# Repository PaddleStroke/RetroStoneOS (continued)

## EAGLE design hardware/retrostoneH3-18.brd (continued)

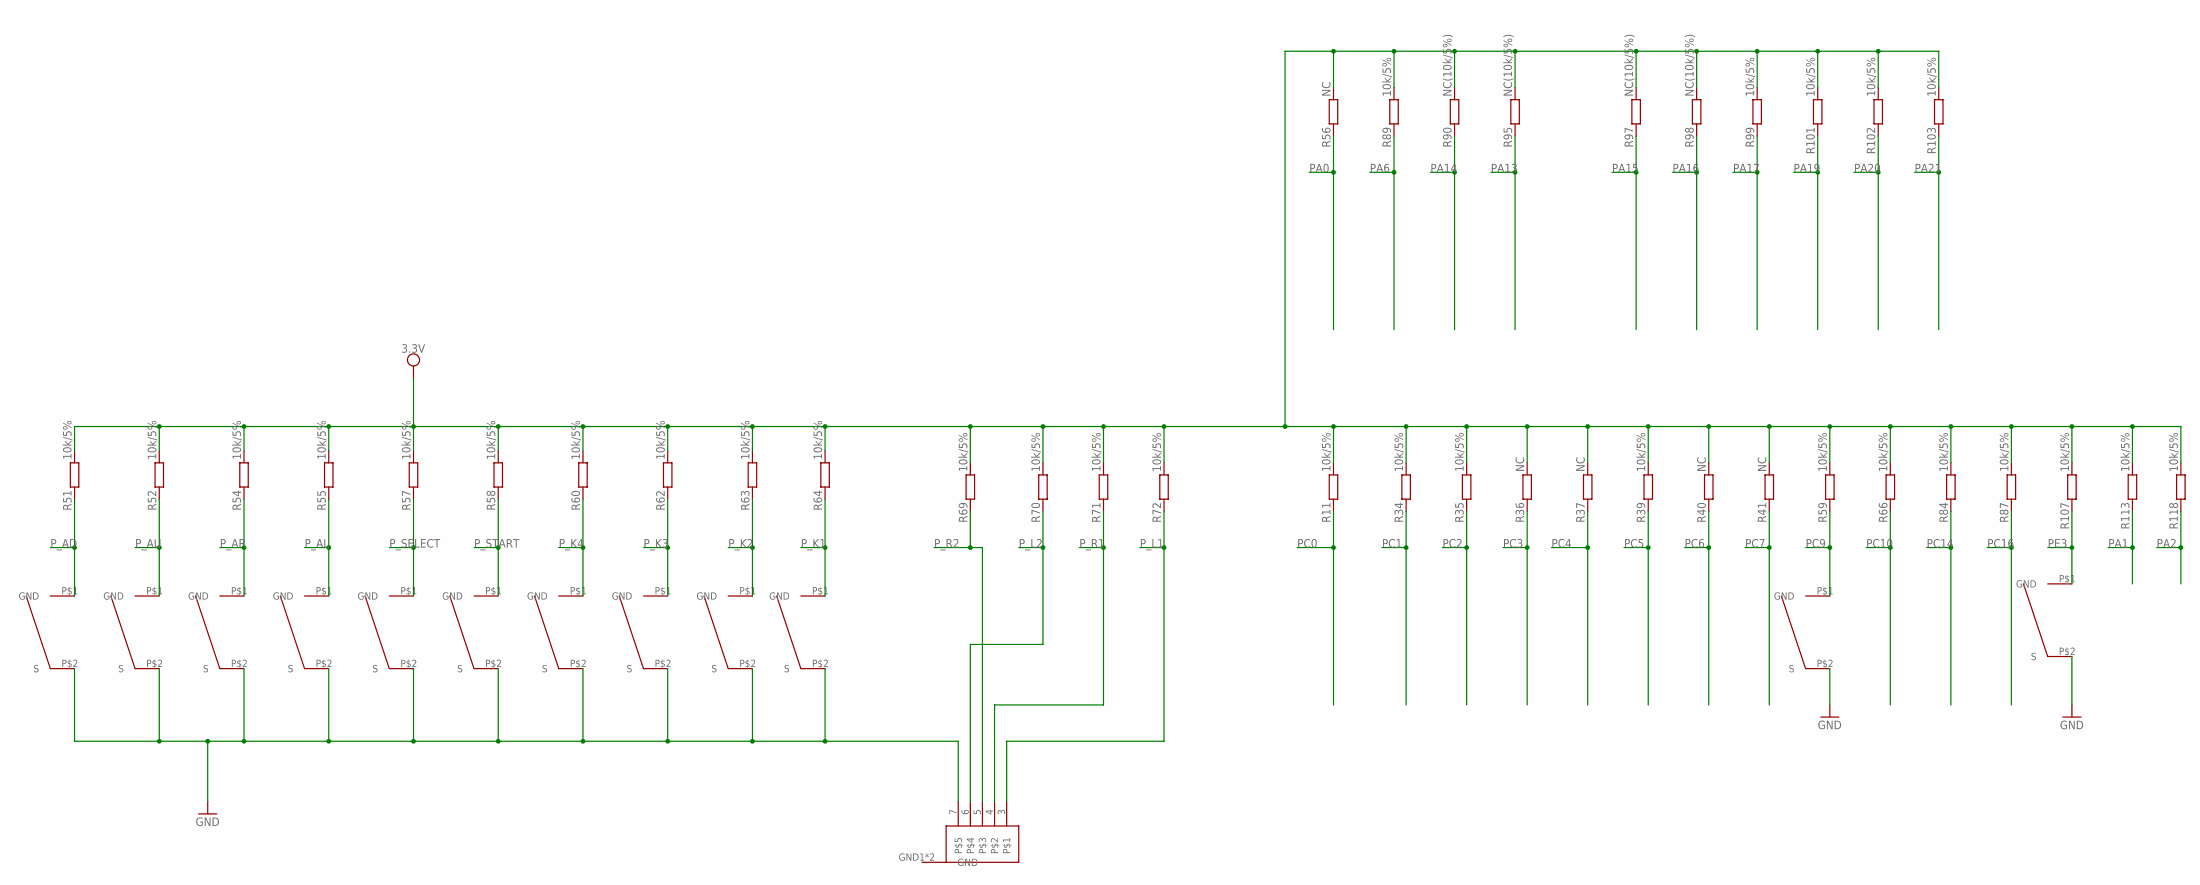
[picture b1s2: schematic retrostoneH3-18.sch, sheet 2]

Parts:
AD: PAD_DIRECTION; PADS_DIRECTION
AL: PAD_DIRECTION; PADS_DIRECTION
AR: PAD_DIRECTION; PADS_DIRECTION
AU: PAD_DIRECTION; PADS_DIRECTION
K1, K2, K3, K4: PAD_BUTTON
R11, R34, R35, R39, R51, R52, R54, R55, R57, R58, R59, R60, R62, R63, R64, R66, R69, R70, R71, R72, R84, R87, R89, R99, R101, R102, R103, R107, R113, R118: 10k/5%; R0402_TI
R36, R37, R40, R41, R56: NC; R0402_TI
R90, R95, R97, R98: NC(10k/5%); R0402_TI
SELECT, SELECT3, SELECT4: PAD_BUTTON
START: PAD_BUTTON
U$4: JST_PH_VERT_5P

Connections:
GND: AD.P$2 (S), AL.P$2 (S), AR.P$2 (S), AU.P$2 (S), K1.P$2 (S), K2.P$2 (S), K3.P$2 (S), K4.P$2 (S), SELECT.P$2 (S), SELECT3.P$2 (S), SELECT4.P$2 (S), START.P$2 (S), U$4.7; also elsewhere on the board
PA0: R56.2; also elsewhere on the board
PA1: R113.2; also elsewhere on the board
PA2: R118.2; also elsewhere on the board
PA6: R89.2; also elsewhere on the board
PA13: R95.2; also elsewhere on the board
PA14: R90.2; also elsewhere on the board
PA15: R97.2; also elsewhere on the board
PA16: R98.2; also elsewhere on the board
PA17: R99.2; also elsewhere on the board
PA19: R101.2; also elsewhere on the board
PA20: R102.2; also elsewhere on the board
PA21: R103.2; also elsewhere on the board
PC0: R11.2; also elsewhere on the board
PC1: R34.2; also elsewhere on the board
PC2: R35.2; also elsewhere on the board
PC3: R36.2; also elsewhere on the board
PC4: R37.2; also elsewhere on the board
PC5: R39.2; also elsewhere on the board
PC6: R40.2; also elsewhere on the board
PC7: R41.2; also elsewhere on the board
PC9: R59.2, SELECT4.P$1 (GND); also elsewhere on the board
PC10: R66.2; also elsewhere on the board
PC14: R84.2; also elsewhere on the board
PC16: R87.2; also elsewhere on the board
PE3: R107.2, SELECT3.P$1 (GND); also elsewhere on the board
P_AD: AD.P$1 (GND), R51.2; also elsewhere on the board
P_AL: AL.P$1 (GND), R55.2; also elsewhere on the board
P_AR: AR.P$1 (GND), R54.2; also elsewhere on the board
P_AU: AU.P$1 (GND), R52.2; also elsewhere on the board
P_K1: K1.P$1 (GND), R64.2; also elsewhere on the board
P_K2: K2.P$1 (GND), R63.2; also elsewhere on the board
P_K3: K3.P$1 (GND), R62.2; also elsewhere on the board
P_K4: K4.P$1 (GND), R60.2; also elsewhere on the board
P_L1: R72.2, U$4.3; also elsewhere on the board
P_L2: R70.2, U$4.6; also elsewhere on the board
P_R1: R71.2, U$4.4; also elsewhere on the board
P_R2: R69.2, U$4.5; also elsewhere on the board
P_SELECT: R57.2, SELECT.P$1 (GND); also elsewhere on the board
P_START: R58.2, START.P$1 (GND); also elsewhere on the board
VCC: R11.1, R34.1, R35.1, R36.1, R37.1, R39.1, R40.1, R41.1, R51.1, R52.1, R54.1, R55.1, R56.1, R57.1, R58.1, R59.1, R60.1, R62.1, R63.1, R64.1, R66.1, R69.1, R70.1, R71.1, R72.1, R84.1, R87.1, R89.1, R90.1, R95.1, R97.1, R98.1, R99.1, R101.1, R102.1, R103.1, R107.1, R113.1, R118.1; also elsewhere on the board

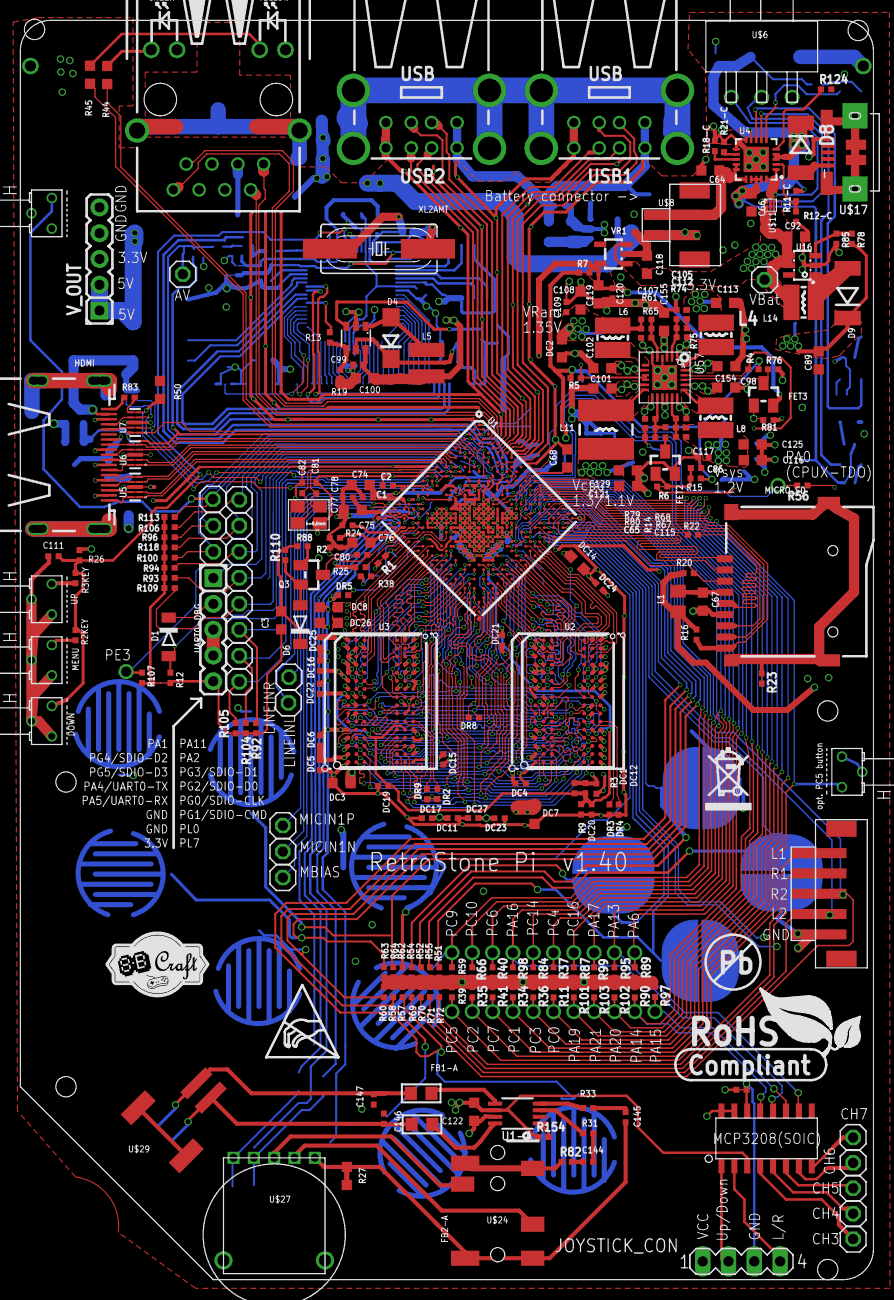
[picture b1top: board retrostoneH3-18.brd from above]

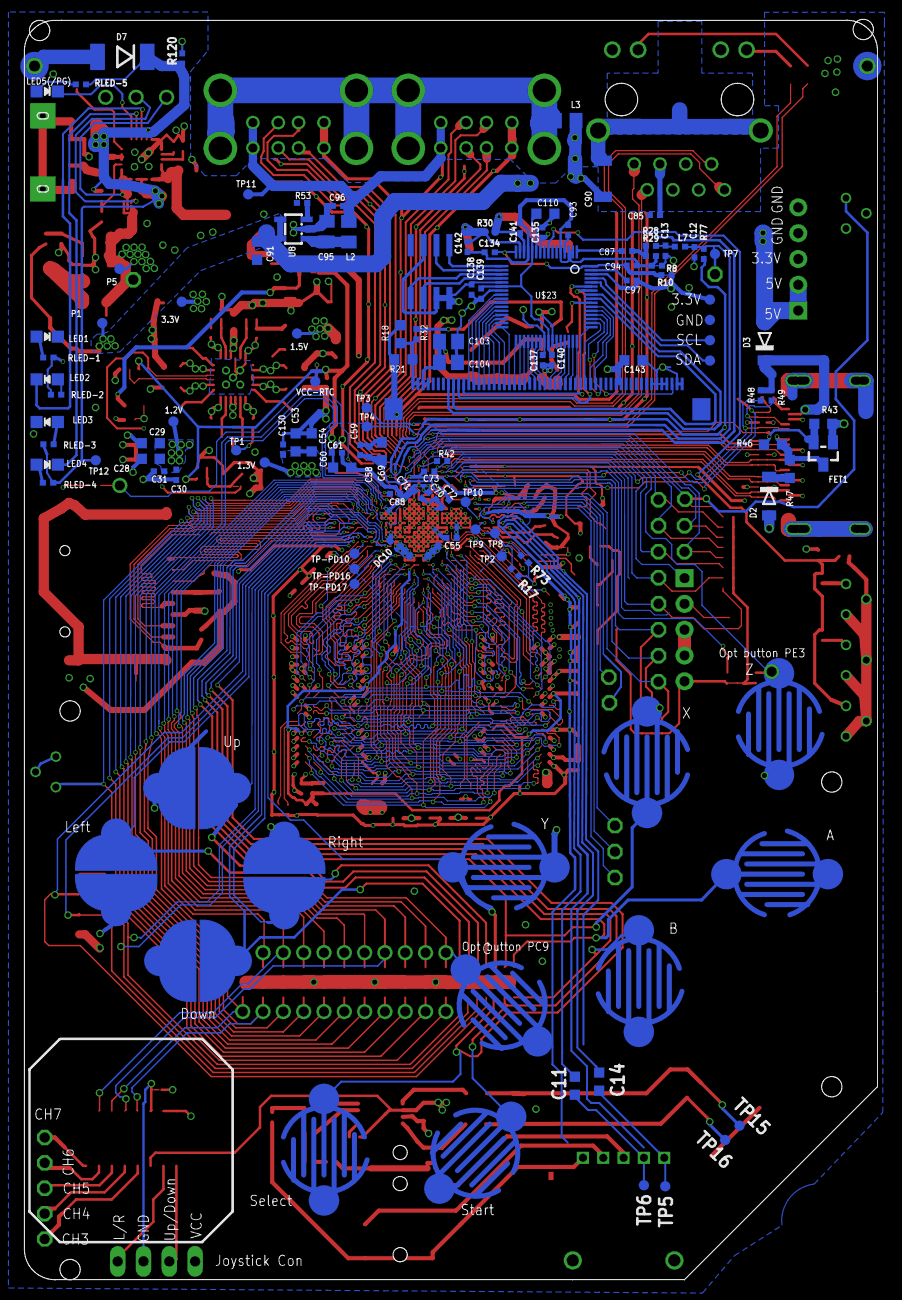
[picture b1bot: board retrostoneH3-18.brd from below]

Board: 4 copper layers, 84.0 x 124.0 mm, 383 parts (126 on the bottom side), 337 nets.

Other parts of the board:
U$9: PB
U$16: 8BCRAFT
U$41: ROHS
U$42: RECYCLE_BIN1/8
U$43: ESD_SYMBOL
